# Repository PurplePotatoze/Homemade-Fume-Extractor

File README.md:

# Homemade-Fume-Extractor
BREATH INN THE SOLDER FUMEESS, or don't with my homemade multimeter 😊.

# CAD

# PCB

# Schematic

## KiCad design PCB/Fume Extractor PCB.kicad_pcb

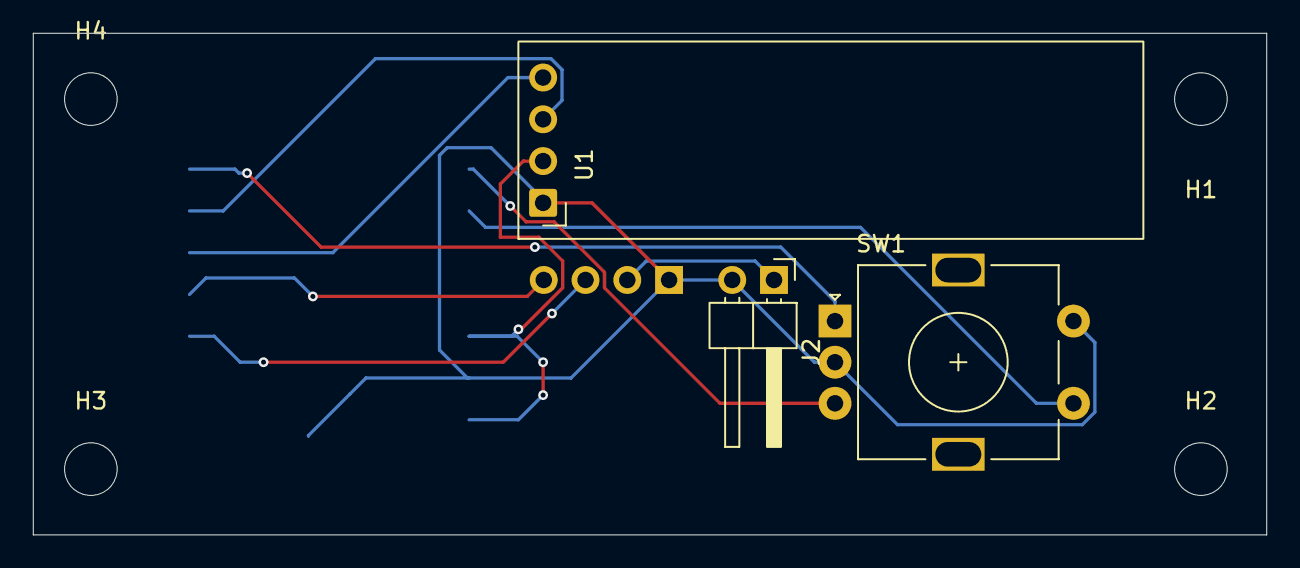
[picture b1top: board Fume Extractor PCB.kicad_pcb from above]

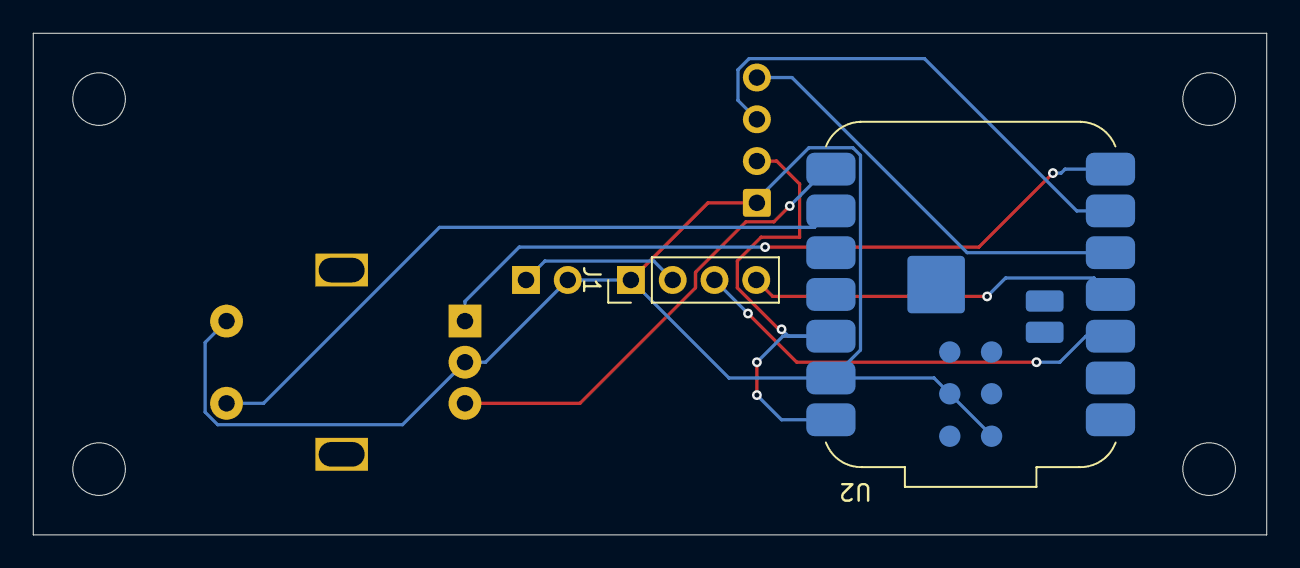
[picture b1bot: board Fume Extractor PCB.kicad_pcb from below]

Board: 2 copper layers, 75.0 x 30.5 mm, 9 parts (2 on the bottom side), 10 nets.

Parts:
H1, H2, H3, H4: MountingHole; MountingHole_3.2mm_M3
J1: Conn_01x04; PinHeader_1x04_P2.54mm_Vertical
J2: Conn_01x02; PinHeader_1x02_P2.54mm_Horizontal
SW1: RotaryEncoder_Switch; RotaryEncoder_Alps_EC11E-Switch_Vertical_H20mm
U1: ER_OLEDM0.91_1x-I2C
U2: XIAO-ESP32-C3-SMD; MCU_Seeed_ESP32C3

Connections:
+3.3V: U1.2 (VCC), U2.12 (3V3_OUT), U2.14 (VBUS)
+12V: J1.2, J2.1
GND: J1.1, J2.2, SW1.C, SW1.S2, U1.1 (GND), U2.13 (GND), U2.18 (GND), U2.22 (GND)
unnamed: J1.3, U2.3 (D2)
unnamed: J1.4, U2.4 (D3)
unnamed: U1.3 (SCL), U2.6 (D5)
unnamed: U1.4 (SDA), U2.5 (D4)
unnamed: SW1.A, U2.7 (D6)
unnamed: SW1.B, U2.8 (D7)
unnamed: SW1.S1, U2.9 (D8)
